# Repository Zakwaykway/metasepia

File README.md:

# Metasepia

An ergogenerated hummingbird-esque keyboard, inspired by jcmkk3's rufous, modified to my taste.

v2 is in development.

## Notable changes
  - Aggressive stagger (especially on index),
  - Wider thumbs,
  - Wireless compatibility,
  - Hotswappable,
  - And a breakable bottom pinky key (bound to top pinky's assignment in v1).

The pcb in v1/production is tested; fully functional with both xiao rp2040 & xiao nrf52840.

ZMK module (wired + wireless firmware) can be found at [zmk-keyboard-metasepia](https://github.com/zakwaykway/zmk-keyboard-metasepia).

front | back
-|-
 | 

## Assembly
### Components
- BOM.md
- If wireless isn't needed: BAT+ pogo, power slider, and battery aren't needed. Reset pogo & button are also optional, as there are other ways to trigger a reset.

### Build guide
0. **Optional:** remove bottom pinky key by cutting its traces, scoring the pcb at the tabs, and snapping off.
1. On **back** face: Tin **ONE** pad of each component.
2. Insert all hotswap sockets, and reflow tinned pads.
3. For diodes, I place and reflow one at a time, because they are a lot smaller & tend to jump around. 
4. Then, solder diodes' and sockets' 2nd (untinned) pads.
5. Solder reset button. 
6. On **front** face: solder slider switch, then MCU sockets.
7. Solder pogos. If male pins aren't soldered to the mcu yet, do that BEFORE adding pogos—doing it after is very tedious and annoying.
8. If careful, it IS POSSIBLE to solder a female JST-PH 2-pin connector. Its legs should be pointed **away** from the MCU (south). It is important that it be placed as close to the MCU as possible, or the plate won't fit over it.
9. **Enjoy your new keyboard!** Send me pics, suggestions, or comments @zakwaykway on discord \:))

## Thanks:
Making metasepia was an intensive learning experience, and a huge pride. 
Thanks to mrzealot for ergogen, ceoloide for their fork of ergogen, flatfootfox for their guide to ergogen; 
To the fingerpunch and 40% keyboard servers for questions and inspiration; 
To jcmkk3 for rufous' ergogen config; 
To ZMK for being an amazing keyboard firmware; 
To my friends, for making the art that's on the board;
And to all who have open-sourced their work, whether pcbs, footprints, or firmware--this wouldn't be possible without you.

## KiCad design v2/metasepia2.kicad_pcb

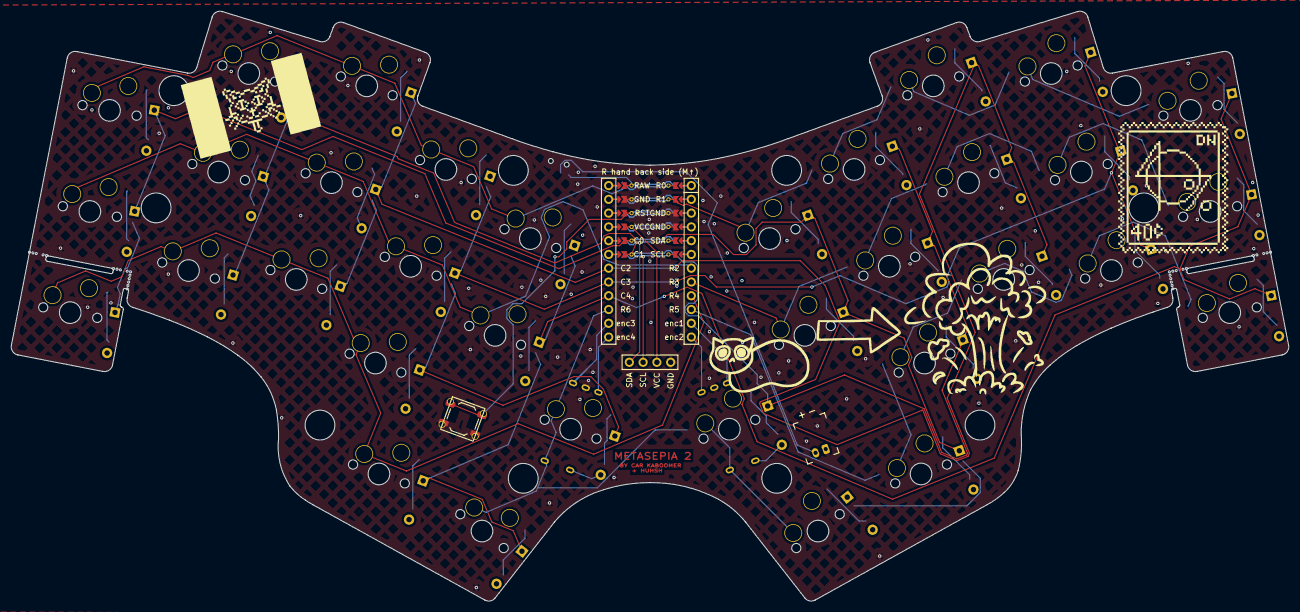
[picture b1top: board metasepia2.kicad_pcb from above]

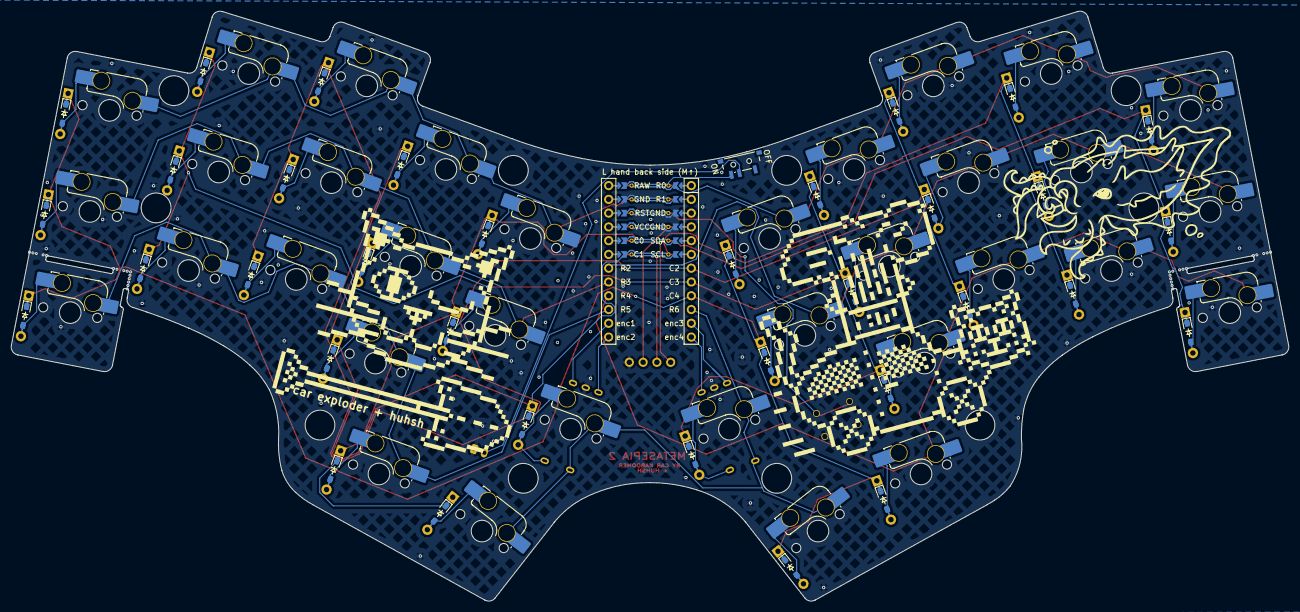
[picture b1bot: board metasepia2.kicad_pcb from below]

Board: 2 copper layers, 235.6 x 108.8 mm, 116 parts (35 on the bottom side), 57 nets.

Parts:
B1: button-alps-skqg
DISP1: display_ssd1306
JST1: battery_connector_jst_ph_2
MCU1: mcu_nice_nano
MH1, MH2, MH3, MH5, MH6, MH7, MH8, MH9, MH11, MH12, MH13, MH14, MH16, MH17, MH18, MH19, MH20, MH21, MH23, MH24, MH25, MH26, MH27, MH28, MH29, MH30, MH31, MH32, MH33, MH34, MH35, MH36, MH37, MH38, MH39, MH40, MH41, MH42, MH43, MH44: mounting_hole_npth
PWR1: power_switch_smd_side
RE1, RE2: rotary_encoder_ec11_ec12
XX1, XX2, XX3, XX4, XX5, XX6, XX7, XX8, XX9, XX10, XX11, XX12, XX13, XX14, XX15, XX16, XX17, XX18, XX19, XX20, XX21, XX22, XX23, XX24, XX25, XX26, XX27, XX28, XX29, XX30, XX31, XX32, XX33, XX34: hs-mx
XX35, XX36, XX37, XX38, XX39, XX40, XX41, XX42, XX43, XX44, XX45, XX46, XX47, XX48, XX49, XX50, XX51, XX52, XX53, XX54, XX55, XX56, XX57, XX58, XX59, XX60, XX61, XX62, XX63, XX64, XX65, XX66, XX67, XX68: diode_tht
XX69: button-6x6

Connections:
C0: MCU1.120, XX35.2, XX36.2, XX37.2, XX61.2, XX62.2, XX65.2, XX66.2
C1: MCU1.119, XX38.2, XX39.2, XX40.2, XX58.2, XX59.2, XX60.2, XX68.2
C2: MCU1.18, XX41.2, XX42.2, XX43.2, XX55.2, XX56.2, XX57.2
C3: MCU1.17, XX44.2, XX45.2, XX46.2, XX52.2, XX53.2, XX54.2, XX67.2
C4: MCU1.16, XX47.2, XX48.2, XX49.2, XX50.2, XX51.2, XX63.2, XX64.2
GND: B1.2, DISP1.4, JST1.1, MCU1.103, MCU1.104, MCU1.123, RE1.B, RE2.B, XX69.2
R0: MCU1.101, XX3.1, XX6.1, XX9.1, XX12.1, XX14.1
R1: MCU1.102, XX17.1, XX20.1, XX23.1, XX26.1, XX28.1
R2: MCU1.7, XX2.1, XX5.1, XX8.1, XX11.1, XX13.1
R3: MCU1.8, XX16.1, XX19.1, XX22.1, XX25.1, XX27.1
R4: MCU1.9, XX1.1, XX4.1, XX7.1, XX10.1, XX29.1
R5: MCU1.10, XX15.1, XX18.1, XX21.1, XX24.1, XX31.1
R6: MCU1.15, RE1.S2, RE2.S2, XX30.1, XX32.1, XX33.1, XX34.1
RAW: MCU1.124, PWR1.3
RST: B1.1, MCU1.122, XX69.1
SCL: DISP1.2, MCU1.106
SDA: DISP1.1, MCU1.105
VCC: DISP1.3, MCU1.121
battery: JST1.2, PWR1.2
default_default: RE1.S1, XX33.2, XX67.1
enc1: MCU1.14, RE1.A
enc2: MCU1.13, RE1.C
enc3: MCU1.12, RE2.A
enc4: MCU1.11, RE2.C
index_bottom: XX10.2, XX44.1
index_home: XX11.2, XX45.1
index_top: XX12.2, XX46.1
inner_home: XX13.2, XX47.1
inner_top: XX14.2, XX48.1
middle_bottom: XX7.2, XX41.1
middle_home: XX8.2, XX42.1
middle_top: XX9.2, XX43.1
mirror_default_default: RE2.S1, XX34.2, XX68.1
mirror_index_bottom: XX24.2, XX58.1
mirror_index_home: XX25.2, XX59.1
mirror_index_top: XX26.2, XX60.1
mirror_inner_home: XX27.2, XX61.1
mirror_inner_top: XX28.2, XX62.1
mirror_middle_bottom: XX21.2, XX55.1
mirror_middle_home: XX22.2, XX56.1
mirror_middle_top: XX23.2, XX57.1
mirror_pinky_bottom: XX15.2, XX49.1
mirror_pinky_home: XX16.2, XX50.1
mirror_pinky_top: XX17.2, XX51.1
mirror_reachy_default: XX32.2, XX66.1
mirror_ring_bottom: XX18.2, XX52.1
mirror_ring_home: XX19.2, XX53.1
mirror_ring_top: XX20.2, XX54.1
mirror_tucky_default: XX31.2, XX65.1
pinky_bottom: XX1.2, XX35.1
pinky_home: XX2.2, XX36.1
pinky_top: XX3.2, XX37.1
reachy_default: XX30.2, XX64.1
ring_bottom: XX4.2, XX38.1
ring_home: XX5.2, XX39.1
ring_top: XX6.2, XX40.1
tucky_default: XX29.2, XX63.1

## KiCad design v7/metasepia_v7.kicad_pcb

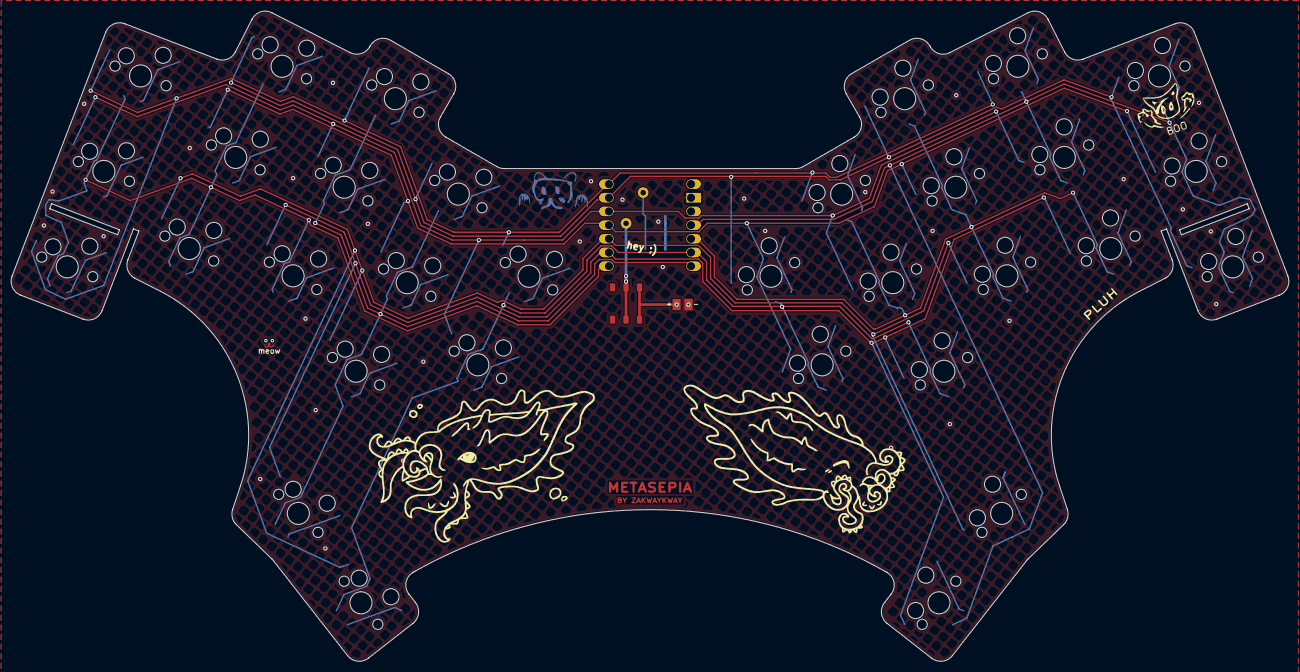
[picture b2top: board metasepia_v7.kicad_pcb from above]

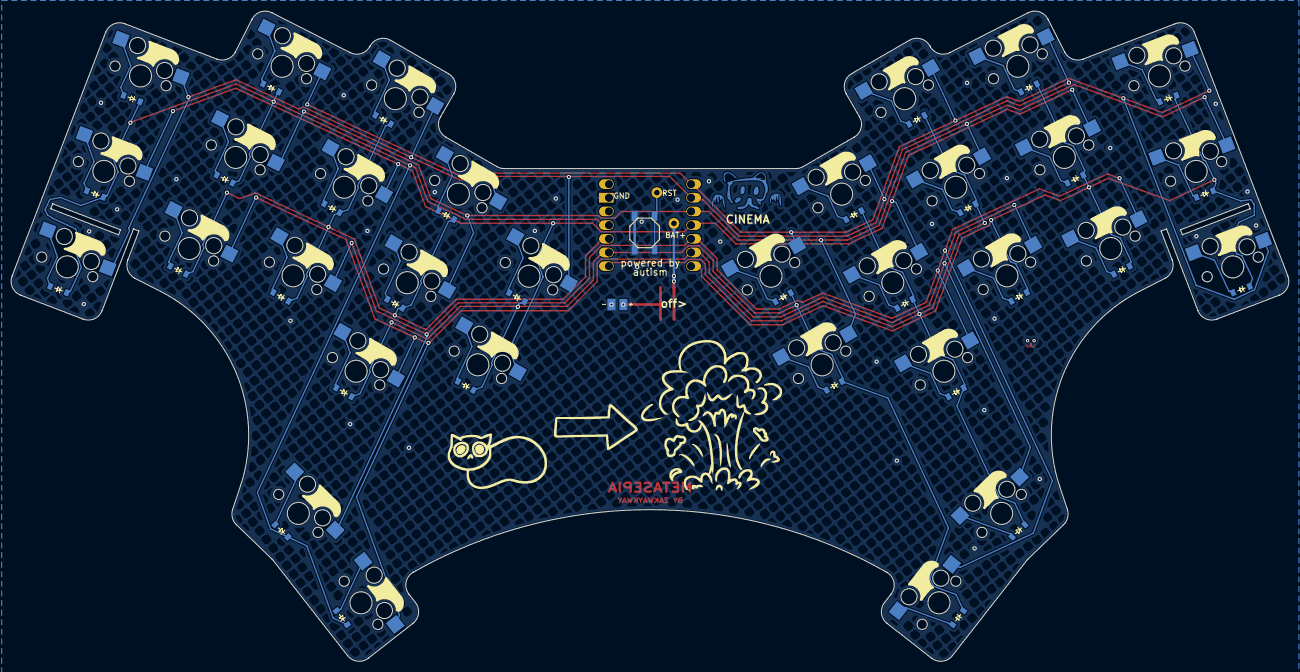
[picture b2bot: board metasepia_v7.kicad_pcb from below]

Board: 2 copper layers, 237.4 x 120.8 mm, 67 parts (64 on the bottom side), 45 nets.

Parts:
B1: SW_TACT_ALPS_SKQGABE010
BT1: Battery_Cell; BatteryPadsReversible
D1, D2, D3, D4, D5, D6, D7, D8, D9, D10, D11, D12, D13, D14, D15, D16, D17, D18, D19, D20, D21, D22, D23, D24, D25, D26, D27, D28, D29, D30, D31, D32: diode_tht_sod123
MCU1: xiao-ble; xiao-pogo
S1, S2, S3, S4, S5, S6, S7, S8, S9, S10, S11, S12, S13, S14, S15, S16, S17, S18, S19, S20, S21, S22, S23, S24, S25, S26, S27, S28, S29, S30, S31, S32: switch_mx

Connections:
GND: B1.2, BT1.2, MCU1.13
P0: MCU1.1, S1.1, S3.1, S9.1, S14.1, S20.1, S26.1
P1: MCU1.2, S6.1, S12.1, S15.1, S17.1, S23.1, S28.1
P2: MCU1.3, S2.1, S8.1, S13.1, S19.1, S25.1
P3: MCU1.4, S5.1, S11.1, S16.1, S22.1, S27.1
P4: MCU1.5, S4.1, S10.1, S21.1, S30.1, S31.1
P5: MCU1.6, S7.1, S18.1, S24.1, S29.1, S32.1
P6: D1.1, D2.1, D3.1, D4.1, D5.1, D6.1, D7.1, MCU1.7
P7: D8.1, D9.1, D10.1, D11.1, D12.1, D29.1, MCU1.8
P8: D13.1, D14.1, D24.1, D27.1, D28.1, D30.1, MCU1.9
P9: D18.1, D21.1, D22.1, D23.1, D25.1, D26.1, MCU1.10
P10: D15.1, D16.1, D17.1, D19.1, D20.1, D31.1, D32.1, MCU1.11
RST: B1.1, MCU1.18
index_bottom: D10.2, S10.2
index_home: D11.2, S11.2
index_top: D12.2, S12.2
inner_home: D13.2, S13.2
inner_top: D14.2, S14.2
middle_bottom: D7.2, S7.2
middle_home: D8.2, S8.2
middle_top: D9.2, S9.2
mirror_index_bottom: D24.2, S24.2
mirror_index_home: D25.2, S25.2
mirror_index_top: D26.2, S26.2
mirror_inner_home: D27.2, S27.2
mirror_inner_top: D28.2, S28.2
mirror_middle_bottom: D21.2, S21.2
mirror_middle_home: D22.2, S22.2
mirror_middle_top: D23.2, S23.2
mirror_pinky_bottom: D15.2, S15.2
mirror_pinky_home: D16.2, S16.2
mirror_pinky_top: D17.2, S17.2
mirror_reachy_default: D32.2, S32.2
mirror_ring_bottom: D18.2, S18.2
mirror_ring_home: D19.2, S19.2
mirror_ring_top: D20.2, S20.2
mirror_tucky_default: D31.2, S31.2
pinky_bottom: D1.2, S1.2
pinky_home: D2.2, S2.2
pinky_top: D3.2, S3.2
reachy_default: D30.2, S30.2
ring_bottom: D4.2, S4.2
ring_home: D5.2, S5.2
ring_top: D6.2, S6.2
tucky_default: D29.2, S29.2

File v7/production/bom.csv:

Designator,Footprint,Quantity,Value,LCSC Part #
B1,SW_TACT_ALPS_SKQGABE010,1,,
BT1,BatteryPadsReversible,1,Battery_Cell,
"D1, D10, D11, D12, D13, D14, D15, D16, D17, D18, D19, D2, D20, D21, D22, D23, D24, D25, D26, D27, D28, D29, D3, D30, D31, D32, D4, D5, D6, D7, D8, D9",diode_tht_sod123,32,,
MCU1,xiao-pogo,1,xiao-ble,
"S1, S10, S11, S12, S13, S14, S15, S16, S17, S18, S19, S2, S20, S21, S22, S23, S24, S25, S26, S27, S28, S29, S3, S30, S31, S32, S4, S5, S6, S7, S8, S9",switch_mx,32,,

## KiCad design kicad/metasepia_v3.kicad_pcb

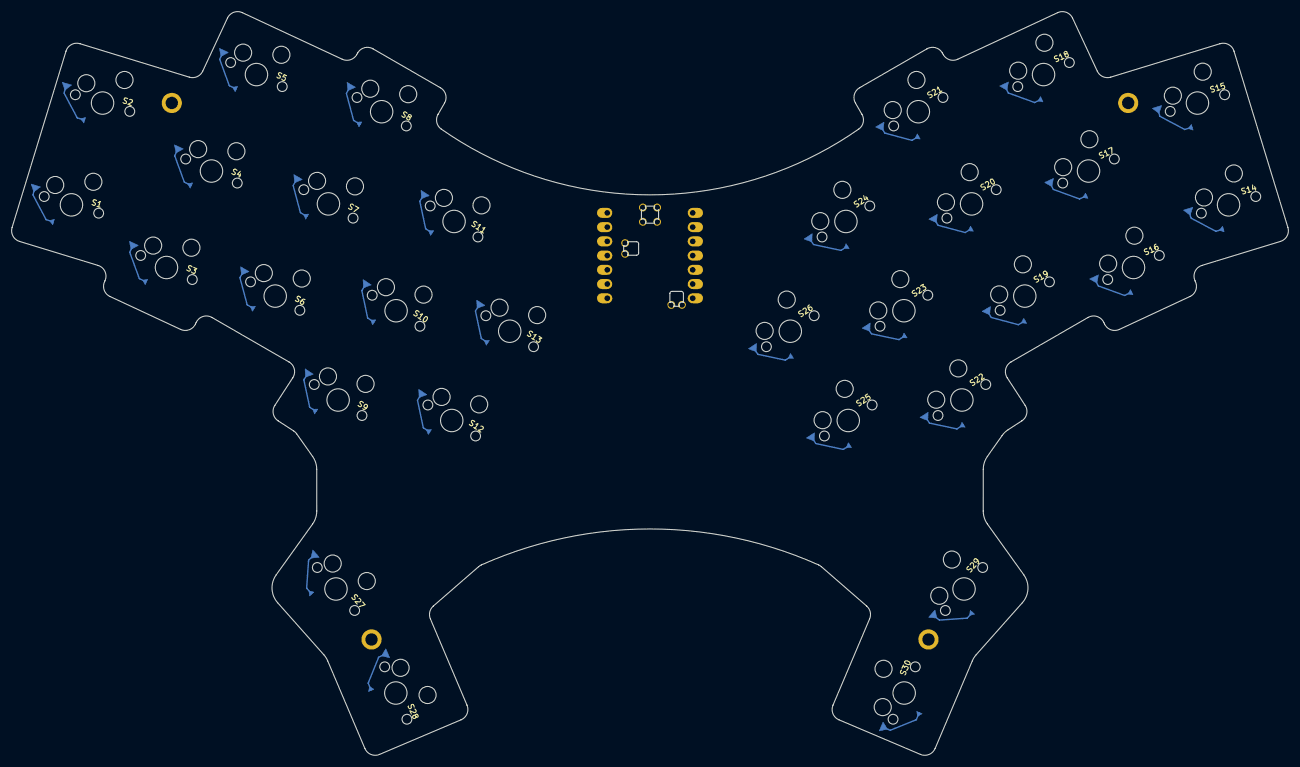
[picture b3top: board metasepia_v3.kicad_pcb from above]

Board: 2 copper layers, 227.9 x 132.7 mm, 35 parts (0 on the bottom side), 7 nets, no tracks yet.

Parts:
MCU1: xiao-ble; xiao-smd
S1, S2, S3, S4, S5, S6, S7, S8, S9, S10, S11, S12, S13, S14, S15, S16, S17, S18, S19, S20, S21, S22, S23, S24, S25, S26, S27, S28, S29, S30: MX
_1, _2, _3, _4: m2hole

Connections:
GND: MCU1.13, MCU1.17
P0: MCU1.1, S2.1, S8.1, S13.1, S18.1, S24.1
P1: MCU1.2, S5.1, S11.1, S15.1, S21.1, S26.1
P2: MCU1.3, S1.1, S7.1, S12.1, S17.1, S23.1
P3: MCU1.4, S4.1, S10.1, S14.1, S20.1, S25.1
P4: MCU1.5, S3.1, S9.1, S19.1, S28.1, S29.1
P5: MCU1.6, S6.1, S16.1, S22.1, S27.1, S30.1

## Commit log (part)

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2025-02-17 create matasepia.yaml
    first commit
2025-02-17 Create from_scratch.yaml
    matasepia
2025-02-24 Create BOM
2025-02-25 Update and rename rufous.yaml to rufous-based.yaml
    need to figure out how to configure the footprints in troch.pretty. Then everything will make sense.
2025-02-26 correct name
2025-02-26 Add kicad footprints to matasepia repo
2025-02-26 add .gitignore to ignore unnecessary files
2025-02-26 finally fix gitignore to ignore .DS_Store?
2025-02-26 Remove .DS_Store from repo
2025-02-26 Remove .DS_Store and reorg footprint folder
2025-02-26 cleaning stuff up, correct config location
2025-02-26 Add ergogen footprints
2025-02-26 Add project files
2025-02-26 update bom 'made with autism'
2025-02-27 syncing to desktop app
2025-02-28 solve kicad outline errors
2025-02-28 Refining pcb for compatibility
    - non-ceoloide-dependant mountinghole footprint, added to ergogen footprints
    -corrected bad outline for pcb
    renamed some folders to be more accurate
2025-02-28 Solving for push
2025-02-28 correct matesepia to metasepia everywhere
2025-03-01 Define new footprints in kicad
    customized diode; customized hotswap socket; customized xiao footprints. Created "frequent.pretty" footprint library for custom fp's. Next steps: art and routing.
2025-03-01 test diode fp. PRobably not gonna use
2025-03-01 fix routing disappearing
2025-03-01 beginning routing in kicad. Minor footprint edits.
2025-03-01 routed, badly. All diodes are fucked. Need redo.
2025-03-01 properly remaking traces from scratch. Half done.
2025-03-01 clearing up kicad files
2025-03-02 almost finish routing
2025-03-02 clarification
2025-03-02 Update BOM
2025-03-05 create metasepia2, edit diode footprint
2025-03-05 metasepia2
2025-03-05 rename and optimize ergogen footprints
2025-03-05 fully route metasepiav2
2025-03-06 changes to pcb
2025-03-06 update bom, ergogen; tweak pcb
    set j value in ergogen config to 0. Hotswap sockets don't need vertical padding.
2025-03-10 test add battery pads ergogen
2025-03-14 create metasepia v3 ergogen config
2025-03-14 test
2025-03-15 update mtsp3
2025-03-16 add metasepia art v1 from S
2025-03-18 edit metasepia v3 and new ki footprints
2025-03-19 create metasepia v3 pcb
    no wiring, init
2025-03-19 wire metasepia3, create slider footprint, update footprints
2025-03-19 update bom, optimize kicad tree
2025-03-20 create slider switch, battery pad, add to v3
2025-03-28 create v4 ergogen
2025-04-23 metasepia5 create
2025-04-29 update gitignore & metasepia5
2025-04-30 begin kicadding metasepia5
2025-04-30 Delete kicad backups directories
    Delete kicad backups directories
    Delete kicad backups directories
    Delete kicad backups directories
    Delete kicad backups directories
    Delete kicad/v4/fp-info-cache
    Delete kicad/v3/fp-info-cache
2025-05-02 pogo footprint part 1, begin tracing
2025-05-03 more metasepia5 routing, fix net issue in ergogen
    ergogen: must explicitly be `colrow` in pcb section
2025-05-07 xiao-pogo fp and a bit of routing
2025-05-08 almost finish routing v5
2025-05-09 metasepia5 finish
2025-05-09 bom, try plate
    plate gerber no workie, despite 3d render in kicad working
2025-05-10 work on plate and change pcb accordingly
2025-05-10 tweak pcb grounding
2025-05-20 update mx footprint
2025-05-20 change organization
    ergogen configs now in each version of metasepias
2025-06-18 init v6
2025-06-18 change for new file structure testing for v5 at school
2025-06-18 add existing files
2025-06-18 remove ignored files from tracking
2025-06-18 track BOM
2025-06-18 shift in courtyard
2025-06-26 Create metasepia7.yaml
    no wireless support!
2025-06-30 fix reset and gnd's positions
2025-06-30 move metasepia7, SUCCESSFULLY ADD breakoff cutouts
2025-06-30 7 adjust breakoff sizes & polygon
2025-07-06 xiao footprint without bat, adjust thumb, etc
2025-07-08 update metasepia7
2025-07-09 Update metasepia7.yaml and add KiCad project files
    FINAL metasepia7 layout. Only matrix changes from now on.
2025-07-09 finish routing, clear bugged circles
    all that's left is art
2025-07-12 Add artwork and update footprints on PCB
    Added 'METASEPIA', 'LOGO', and 'tism' artwork footprints to the PCB. Adjusted the position of the SW_TACT_ALPS_SKQGABE010 footprint. Deleted the metasepia_switchplate.kicad_pro project file and updat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
2025-07-17 finish v7 and switchplate, create production files
2025-07-18 Send to manu
    Finish metasepia7 and send to manufacture.
    Modified BatteryPadsReversible footprint to use rectangular SMD pads and adjusted silk text positions. Updated metasepia_v7.kicad_pcb with a defined stackup, new net, and minor polygon coordinate cor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
2025-07-22 make breakoff tabs 2mm (were 1mm)
2025-07-22 Update PCB and reorganize production files
    renamed prod pcb files from v7/production to v7/production_pcb, and it is revised
2025-08-19 upload v8.yaml
2025-08-21 remove many footprints
2025-08-24 update gitignore
2025-08-24 add many new footprints, delete many unused footprints, reorganize
2025-08-25 still in progress
2025-08-25 Revert "still in progress"
    This reverts commit d55e459fb3776f144bfdd0175a0e3109473bb6ec.
2025-08-25 Revert "still in progress"
    This reverts commit 139ee74a9803cc27602cdceef3ab012820a93918.
2025-09-04 Remove temp.yaml from v6 directory
    Deleted the v6/temp.yaml file, which contained keyboard layout and PCB configuration data. This may be part of a cleanup or refactor to remove unused or obsolete configuration files.
2025-09-15 new footprints and small mods
2025-09-21 add bat54c footprint
2025-09-22 ergogen footprint tweaks, new placeholder footprint
2025-09-22 bigger pads on slider
2025-10-01 upload new footprints
2025-10-01 rename footprints and tweaks
2025-10-08 Make reversible and add keepout zones
2025-10-08 move footprint to storage
2025-10-08 save work
2025-10-09 Complete xiao pogo reversible
    changed pads' positions to be 100% precise based on "bottom.dxf" from seeed's xiao resources
2025-10-11 rename hsmx
2025-10-11 improve combo switch, add it to ergogen with genteure's tool
2025-10-11 footprint improvements
2025-10-17 footprint changes
2025-10-18 Photos of metaseia
    :)
2025-10-18 Test add an image
2025-10-24 fully jumper xiao
2025-10-24 clean up ergogen xiao footprint
2025-10-31 Images :3
2025-11-08 new footprint: cr2032 holder
2025-11-15 post-production restructuring
2025-11-15 update sw_combo
2025-11-19 pull kicad & ergogen footprints up to date
2025-11-20 Proper path for images
2025-11-20 add tht_button, add comment to cr2032
2025-11-21 add footprint designators
2025-11-21 rename images & upload new images
2025-11-21 fix bom & images in readme
2025-11-21 relocate archive to sit in pcb/
2025-12-02 add circle in cr2032
2025-12-02 add template: kicad8 to prevent bugged config
2025-12-17 rename footprints; redo bs-8 footprint; add reversible slider
2026-02-09 move footprints to new repo
2026-02-09 move all to v1, in preparation for v2
2026-02-09 Add new images. Update README, including a full build guide.
2026-02-18 saving progress
2026-04-22 finalize ergogen config for meta2
2026-04-22 prepare meta2 kicad phase
2026-04-22 finalize meta2 pcb
2026-04-22 thicc plate for meta2 upload
2026-04-22 sending meta2 to be produced
